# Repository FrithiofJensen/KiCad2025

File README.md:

# KiCad 2025 - Fra schematic til PCB til ESP-NOW RC System

Velkommen til materialerne for KiCad 2025 seminaret afholdt af Gert Lauritsen. Dette repository indeholder eksempler, projektfiler og Arduino-kode specifikt fokuseret på design af et printkort (PCB) til et fjernstyringssystem (RC) baseret på ESP-NOW protokollen.

Formålet med seminaret er at demonstrere designflowet i KiCad – fra skematisk diagram til færdigt PCB-layout – med et konkret projekt som eksempel: design af hardware til en ESP-NOW baseret sender eller modtager.

Vi vil se på, hvordan man designer et printkort, der integrerer en ESP32 microcontroller sammen med nødvendige komponenter som f.eks. input-enheder (joysticks, knapper) til en sender, eller output-drivere (servo-stik, motor-drivere) til en modtager. De medfølgende `.ino` filer implementerer selve ESP-NOW kommunikationen.

## Indhold

Repository'et indeholder (eller vil indeholde) følgende:

*   **KiCad Projektfiler:**
    *   Eksempler på skematiske diagrammer (`.kicad_sch`) for en RC-sender og/eller modtager.
    *   Eksempler på PCB layouts (`.kicad_pcb`) tilpasset ESP-moduler og RC-komponenter.
    *   Projektfil (`.kicad_pro`).
*   **Biblioteksfiler:**
    *   Specifikke symboler (`.kicad_sym`) og footprints (`.kicad_mod`) brugt i eksemplerne (hvis de ikke er standard i KiCad).
*   **ESP-NOW RC Arduino Sketches (`.ino`):**
    *   `RcRemote.ino`: Kode til ESP32 **senderen**. Læser typisk inputs (f.eks. fra potentiometre/joystick på det designede PCB) og sender data via ESP-NOW.
    *   `RCModtager.ino`: Kode til ESP32 **modtageren**. Modtager data via ESP-NOW og styrer outputs (f.eks. servoer eller motorer, potentielt via det designede PCB).
    *   Disse filer er beregnet til at blive kompileret og uploadet via Arduino IDE til separate ESP32 boards.
*   **Gerber/Produktionsfiler (Eksempel):**
    *   Eksempler på output-filer (`.gbr`, `.drl`) til PCB-produktion.

## Forudsætninger

For at få det fulde udbytte af seminaret og materialerne anbefales følgende software og hardware:

*   **Software:**
    *   **KiCad:**  Den seneste stabile version anbefales. Kan downloades gratis fra [https://www.kicad.org/](https://www.kicad.org/).
    *   **Arduino IDE:** Nødvendig for at arbejde med `.ino` filerne. Kan downloades gratis fra [https://www.arduino.cc/en/software](https://www.arduino.cc/en/software).
        *   **VIGTIGT:** Sørg for at have **ESP8266** og/eller **ESP32 board support** installeret i Arduino IDE via "Boards Manager". Se guides online, f.eks.:
            *   ESP32: [Howto install ESP32](https://randomnerdtutorials.com/installing-esp32-arduino-ide-2-0/)
        *   Tjek `.ino` filerne for eventuelle yderligere nødvendige Arduino libraries (ud over ESP-NOW, som er indbygget) og installer dem via "Library Manager".
*   **Hardware:**
    *   **Mindst to ESP32 boards** (f.eks. NodeMCU, ESP32 DevKitC) – ét til senderen og ét til modtageren for at kunne teste ESP-NOW kommunikationen.
    *   (Valgfrit) Komponenter til at bygge prototyper af sender/modtager (breadboard, ledninger, joysticks, potentiometre, servoer etc.).

## Brug af Materialerne

1.  **Klon eller Download:** Hent materialerne ned på din computer ved at klone repository'et (`git clone https://github.com/gert-lauritsen/KiCad2025.git`) eller downloade det som en ZIP-fil.
2.  **KiCad:** Åbn `.kicad_pro` filen i KiCad for at udforske skematik og PCB layout. Brug filerne som reference eller udgangspunkt for dit eget RC-hardware design.
3.  **Arduino / ESP-NOW:**
    *   Åbn `RcRemote.ino` i Arduino IDE.
    *   Åbn `RCModtager.ino` i et andet Arduino IDE vindue (eller efter hinanden).
    *   **Vigtigt:** ESP-NOW kræver, at enhederne kender hinandens MAC-adresser. Du skal typisk finde MAC-adressen på modtager-boardet og indsætte den i koden på sender-boardet (og/eller omvendt, afhængigt af koden). Find instruktioner til dette i kode-kommentarerne eller i ESP-NOW tutorials.
    *   Vælg det korrekte ESP32 board og port i "Tools" menuen for hvert board.
    *   Kompilér og upload sender-koden til det ene board.
    *   Kompilér og upload modtager-koden til det andet board.
    *   Test kommunikationen. Brug evt. Serial Monitor til debugging.

Vi håber, du får et lærerigt og udbytterigt seminar! Husk at installere KiCad, Arduino IDE og ESP board support *inden* seminaret starter for at få mest muligt ud af det.

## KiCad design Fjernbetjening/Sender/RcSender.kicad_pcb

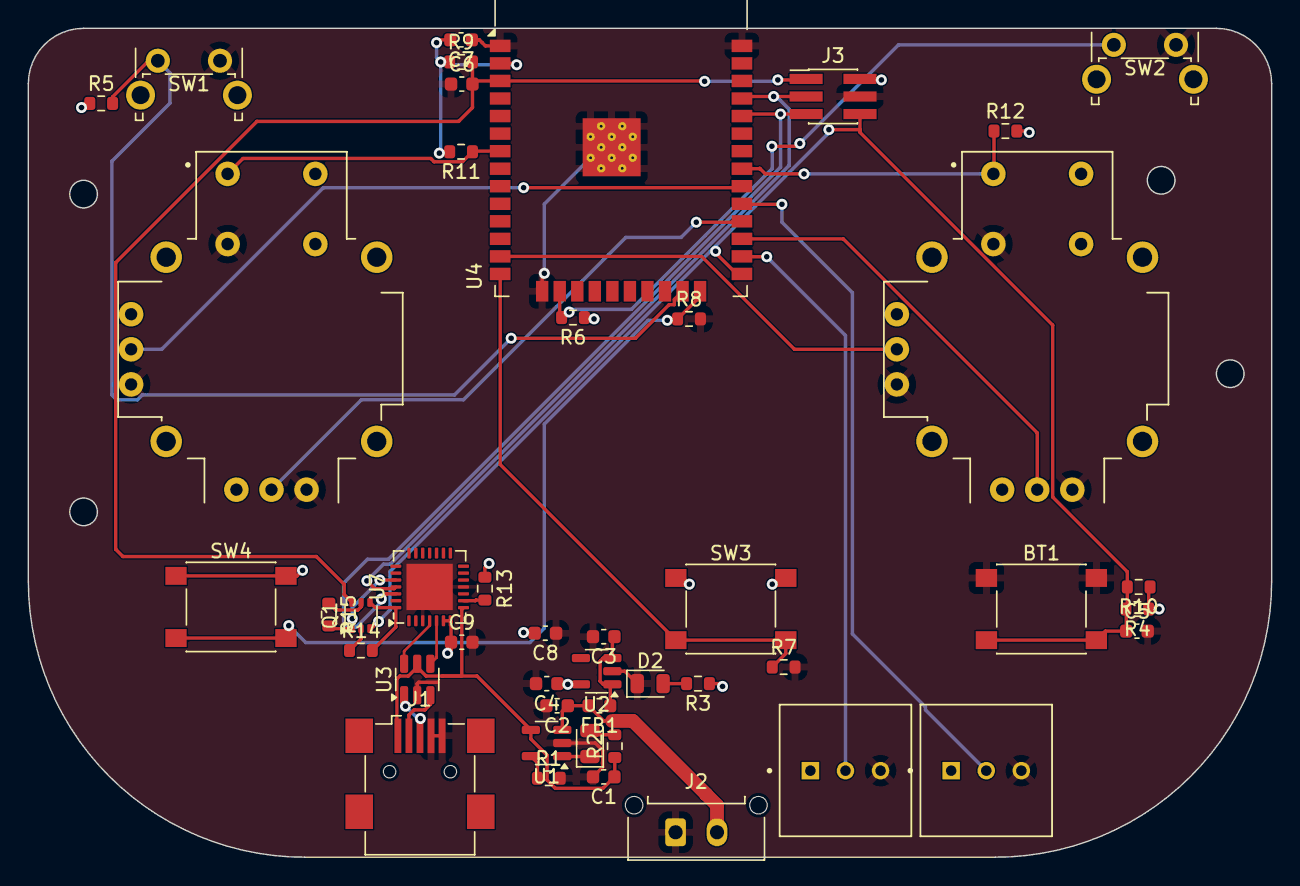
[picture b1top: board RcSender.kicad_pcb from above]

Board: 2 copper layers, 90.0 x 60.0 mm, 45 parts (0 on the bottom side), 34 nets.

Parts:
BT1: SW_Push; SW_SPST_PTS645
C1, C3, C4: 1uF; C_0603_1608Metric
C2: 10nF; C_0603_1608Metric
C5, C6, C7, C8: 0.1uf; C_0603_1608Metric
C9: 10u; C_0603_1608Metric
D1: Chrg; LED_0805_2012Metric
D2: PWR ON; LED_0805_2012Metric
FB1: Ferrite Bead; L_0603_1608Metric
J1: USB_A; USB_Mini-B_Wuerth_65100516121_Horizontal
J2: Bat; Molex_Micro-Fit_3.0_43650-0215_1x02_P3.00mm_Vertical
J3: Prog; PinHeader_2x03_P1.27mm_Vertical_SMD
POT1, POT2: COM-09806; POT-COM_09806
Q1: BC846BS; SOT-363_SC-70-6
R1: 2k; R_0603_1608Metric
R2, R3: 330; R_0603_1608Metric
R4, R5, R6, R7, R8, R11, R12: 4.7k; R_0603_1608Metric
R9, R10: 10K; R_0603_1608Metric
R13: 1k; R_0603_1608Metric
R14, R15: 10k; R_0603_1608Metric
SW1, SW2: SW_Push; SW_Tactile_SPST_Angled_PTS645Vx39-2LFS
SW3, SW4: SW_Push; SW_SPST_PTS645
U1: MCP73832-2-OT; SOT-23-5
U2: AP2112K-3.3; SOT-23-5
U3: USBLC6-2SC6; SOT-23-6
U4: ESP32-WROOM-32
U5, U6: COM-09032; POT-COM-09032
U7: CP2102N-Axx-xQFN28; QFN-28-1EP_5x5mm_P0.5mm_EP3.35x3.35mm

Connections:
+3.3V: C4.1, C7.2, C8.2, C9.1, J3.2, POT1.1, POT2.1, R3.1, R4.1, R5.1, R6.1, R9.1, R10.1, R11.2, R12.2, R13.1, SW3.1, SW4.1, U2.5 (VOUT), U4.2 (VDD), U5.H1 (H+), U5.V1 (V+), U6.H1 (H+), U6.V1 (V+), U7.6 (VDD), U7.7 (VREGIN)
+5V: C1.1, J1.1 (VBUS), R2.1, U1.4 (V_{DD}), U3.5 (VBUS), U7.8 (VBUS)
BT: BT1.2, C5.1, J3.6, Q1.3 (C2), R4.2, R10.2, U4.25 (IO0)
EN: C6.2, J3.1, Q1.6 (C1), R9.2, U4.3 (EN)
GND: BT1.1, C1.2, C2.2, C3.2, C4.2, C5.2, C6.1, C7.1, C8.1, C9.2, D2.1 (K), J1.4 (GND), J1.5 (Shield), J2.1, J3.4, POT1.3, POT2.3, R1.2, R7.2, R8.2, SW1.2, SW2.2, U1.2 (V_{SS}), U2.2 (GND), U3.2 (GND), U4.1 (GND), U4.15 (GND), U4.38 (GND), U4.39 (GND), U5.B2A (SEL-), U5.H3 (H-), U5.V3 (V-), U6.B2A (SEL-), U6.H3 (H-), U6.V3 (V-), U7.3 (GND), U7.11 (~SUSPEND), U7.29 (GND)
IO2: R8.1, SW4.2, U4.24 (IO2)
IO4: POT2.2, U4.26 (IO4)
IO5: POT1.2, U4.29 (IO5)
IO12: R7.1, SW3.2, U4.14 (IO12)
IO13: R6.2, SW2.1, U4.16 (IO13)
IO14: U4.13 (IO14), U6.V2 (V)
IO15: R5.2, SW1.1, U4.23 (IO15)
IO16: U4.27 (IO16), U6.H2 (H)
IO17: U4.28 (IO17), U5.H2 (H)
IO18: U4.30 (IO18), U5.V2 (V)
IO19: R12.1, U4.31 (IO19), U6.B1A (SEL+)
IO35: R11.1, U4.7 (IO35), U5.B1A (SEL+)
unnamed: D1.2 (A), R2.2
unnamed: D1.1 (K), U1.1 (STAT)
unnamed: D2.2 (A), R3.2
unnamed: J1.3 (D+), U3.1 (I/O1)
unnamed: J1.2 (D-), U3.3 (I/O2)
unnamed: Q1.2 (B1), R14.1
unnamed: Q1.1 (E1), R15.2, U7.24 (~RTS)
unnamed: Q1.5 (B2), R15.1
unnamed: Q1.4 (E2), R14.2, U7.28 (~DTR)
unnamed: R1.1, U1.5 (PROG)
unnamed: C3.1, FB1.1, U2.1 (VIN), U2.3 (EN)
unnamed: R13.2, U7.9 (~RST)
RX: J3.5, U4.34 (RXD0/IO3), U7.26 (TXD)
TX: J3.3, U4.35 (TXD0/IO1), U7.25 (RXD)
USBN: U3.4 (I/O2), U7.5 (D-)
USBP: U3.6 (I/O1), U7.4 (D+)
VIN: C2.1, FB1.2, J2.2, U1.3 (V_{BAT})

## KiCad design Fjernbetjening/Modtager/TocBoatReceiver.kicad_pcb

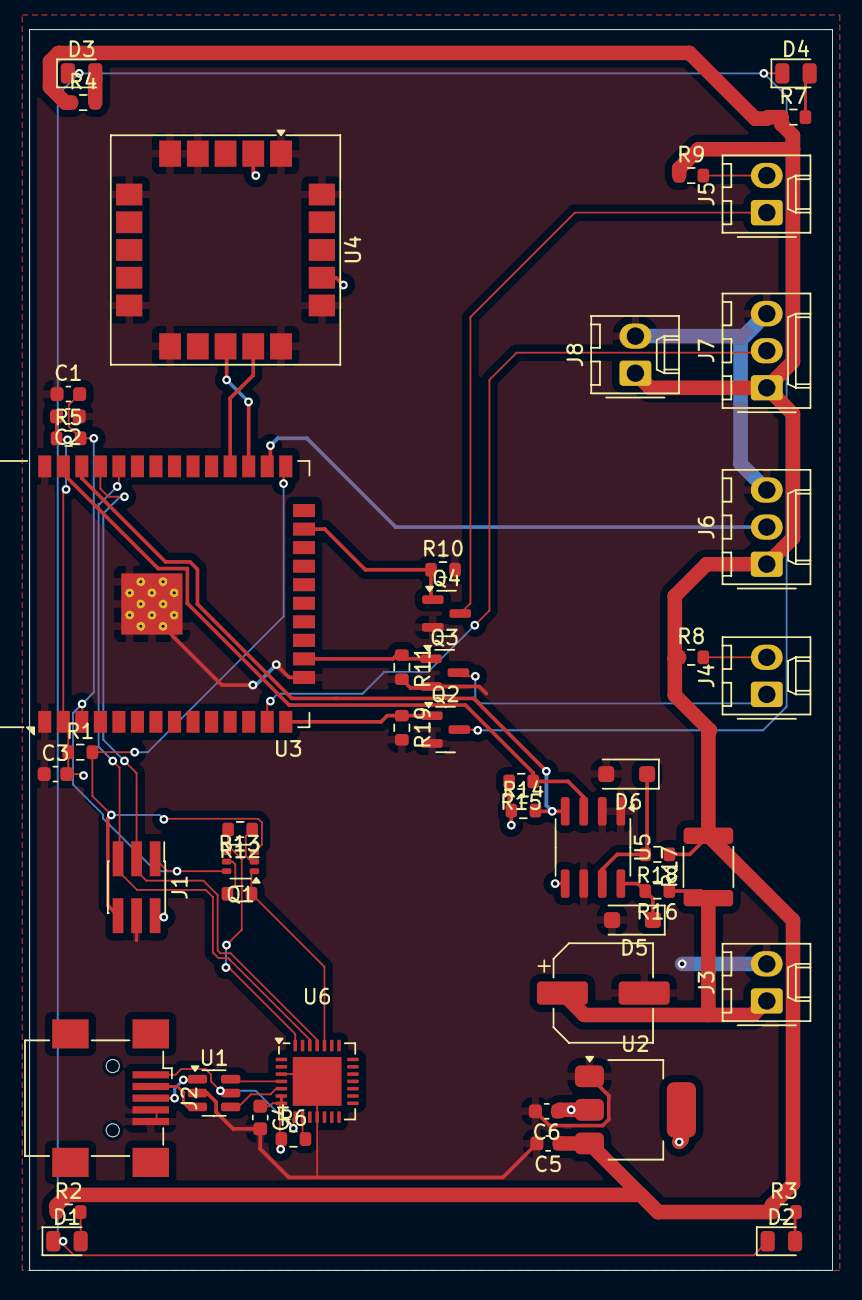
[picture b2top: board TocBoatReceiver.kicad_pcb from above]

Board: 2 copper layers, 55.0 x 85.0 mm, 50 parts (0 on the bottom side), 38 nets.

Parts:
C1, C2, C3: 0.1uf; C_0603_1608Metric
C4: 10u; C_0603_1608Metric
C5, C6: 1u; C_0603_1608Metric
C7: 100uF; CP_Elec_6.3x5.4
D1, D2, D3, D4: LED; LED_0805_2012Metric
D5, D6: BZT52B-C20; D_SOD-123F
J1: Prog; PinHeader_2x03_P1.27mm_Vertical_SMD
J2: USB_A; USB_Mini-B_Wuerth_65100516121_Horizontal
J3: Battery; Molex_KK-254_AE-6410-02A_1x02_P2.54mm_Vertical
J4, J5: Conn_01x02; Molex_KK-254_AE-6410-02A_1x02_P2.54mm_Vertical
J6: SpeedController; Molex_KK-254_AE-6410-03A_1x03_P2.54mm_Vertical
J7: Servo; Molex_KK-254_AE-6410-03A_1x03_P2.54mm_Vertical
J8: PowerESC; Molex_KK-254_AE-6410-02A_1x02_P2.54mm_Vertical
Q1: BC846BS; SOT-363_SC-70-6
Q2, Q3, Q4: AO3400A; SOT-23
R1, R5, R10, R11, R14, R15, R19: 10K; R_0603_1608Metric
R2, R3, R4, R6, R7, R8, R9: 1k; R_0603_1608Metric
R12, R13: 10k; R_0603_1608Metric
R16, R18: 100; R_0603_1608Metric
R17: 0.01R; R_1812_4532Metric
U1: USBLC6-2SC6; SOT-23-6
U2: AP1117-33; SOT-223-3_TabPin2
U3: ESP32-WROOM-32
U4: SAM-M8Q; ublox_SAM-M8Q
U5: INA219BxD; SOIC-8_3.9x4.9mm_P1.27mm
U6: CP2102N-Axx-xQFN28; QFN-28-1EP_5x5mm_P0.5mm_EP3.35x3.35mm

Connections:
+3.3V: C2.2, C3.2, C4.1, C6.1, J1.2, R1.1, R5.1, R6.1, R14.1, R15.2, U2.2 (VO), U3.2 (VDD), U4.2 (VCC_IO), U4.17 (VCC), U5.5 (VS), U6.6 (VDD), U6.7 (VREGIN)
+5V: J2.1 (VBUS), U1.5 (VBUS), U6.8 (VBUS)
+BATT: C5.1, J6.1, J7.1, J8.1, R2.1, R3.1, R4.1, R7.1, R8.1, R9.1, R17.2, R18.1, U2.3 (VI)
/ESP32/GPIO4: J6.2, U3.26 (IO4)
/ESP32/GPIO12: Q2.1 (G), R19.1, U3.14 (IO12)
/ESP32/GPIO13: Q3.1 (G), R11.1, U3.16 (IO13)
/ESP32/GPIO14: J7.2, U3.13 (IO14)
/ESP32/GPIO15: Q4.1 (G), R10.1, U3.23 (IO15)
/ESP32/GPIO16: U3.27 (IO16), U4.13 (TXD)
/ESP32/GPIO17: U3.28 (IO17), U4.14 (RXD)
/ESP32/SCL: R14.2, U3.36 (IO22), U5.4 (SCL)
/ESP32/SDA: R15.1, U3.37 (IO23), U5.3 (SDA)
/USB Serial/USB_N: U1.4 (I/O2), U6.5 (D-)
/USB Serial/USB_P: U1.6 (I/O1), U6.4 (D+)
D0: J1.6, Q1.3 (C2), R1.2, U3.25 (IO0)
EN: C1.2, J1.1, Q1.6 (C1), R5.2, U3.3 (EN)
GND: C1.1, C2.1, C3.1, C4.2, C5.2, C6.2, C7.2, D5.2 (A), D6.2 (A), J1.4, J2.4 (GND), J2.5 (Shield), J3.2, J6.3, J7.3, J8.2, Q2.2 (S), Q3.2 (S), Q4.2 (S), R10.2, R11.2, R19.2, U1.2 (GND), U2.1 (GND), U3.1 (GND), U3.15 (GND), U3.38 (GND), U3.39 (GND), U4.1 (GND), U4.4 (GND), U4.5 (GND), U4.6 (GND), U4.10 (GND), U4.11 (GND), U4.15 (GND), U4.16 (GND), U4.20 (GND), U5.1 (A1), U5.2 (A0), U5.6 (GND), U6.3 (GND), U6.11 (~SUSPEND), U6.29 (GND)
unnamed: D1.2 (A), R2.2
unnamed: D1.1 (K), D2.1 (K), D3.1 (K), D4.1 (K), Q2.3 (D)
unnamed: D2.2 (A), R3.2
unnamed: D3.2 (A), R4.2
unnamed: D4.2 (A), R7.2
unnamed: D5.1 (K), R16.2, U5.8 (IN+)
unnamed: D6.1 (K), R18.2, U5.7 (IN-)
unnamed: J2.3 (D+), U1.1 (I/O1)
unnamed: J2.2 (D-), U1.3 (I/O2)
unnamed: C7.1, J3.1, R16.1, R17.1
unnamed: J4.1, Q3.3 (D)
unnamed: J4.2, R8.2
unnamed: J5.1, Q4.3 (D)
unnamed: J5.2, R9.2
unnamed: Q1.2 (B1), R12.1
unnamed: Q1.1 (E1), R13.2, U6.24 (~RTS)
unnamed: Q1.5 (B2), R13.1
unnamed: Q1.4 (E2), R12.2, U6.28 (~DTR)
unnamed: R6.2, U6.9 (~RST)
RX: J1.5, U3.34 (RXD0/IO3), U6.26 (TXD)
TX: J1.3, U3.35 (TXD0/IO1), U6.25 (RXD)

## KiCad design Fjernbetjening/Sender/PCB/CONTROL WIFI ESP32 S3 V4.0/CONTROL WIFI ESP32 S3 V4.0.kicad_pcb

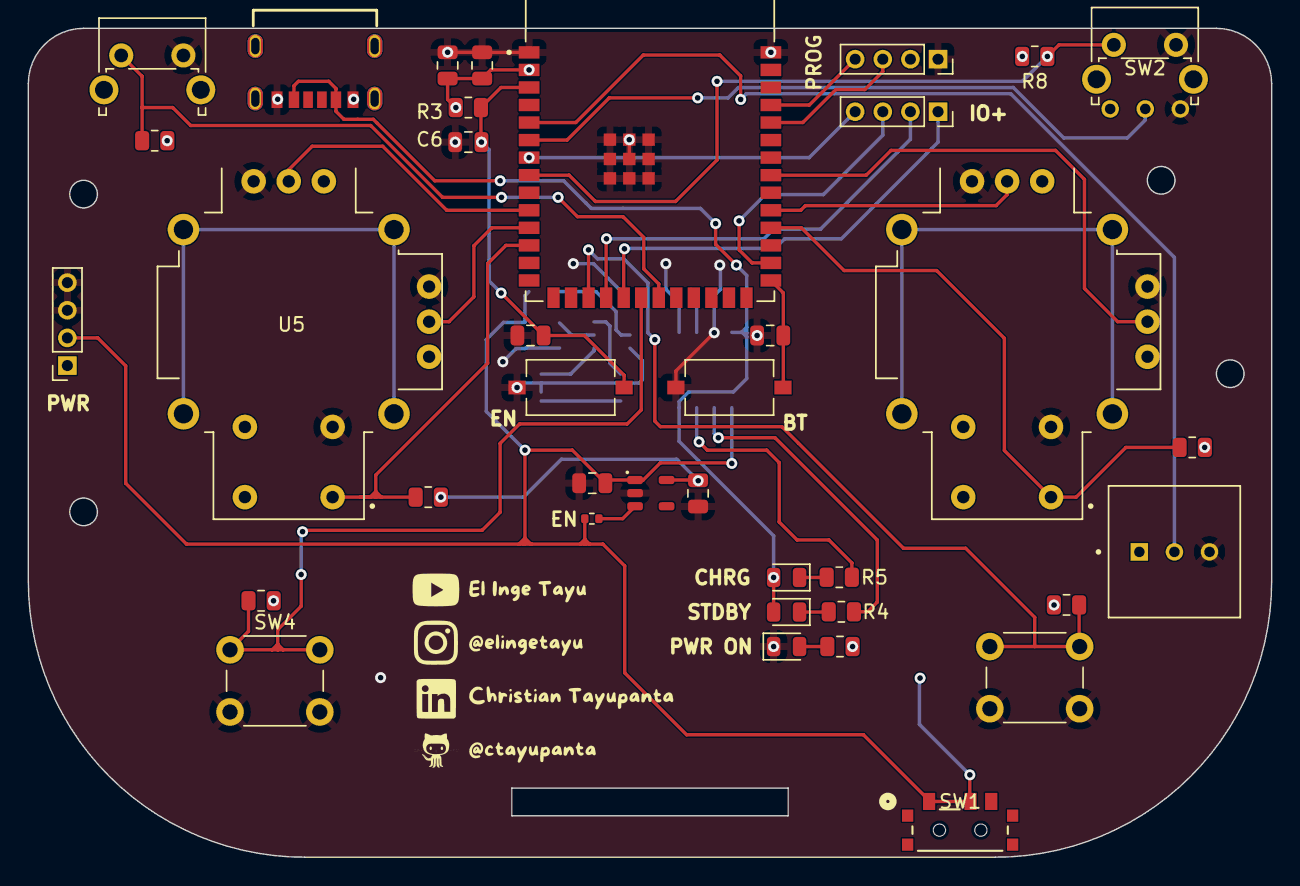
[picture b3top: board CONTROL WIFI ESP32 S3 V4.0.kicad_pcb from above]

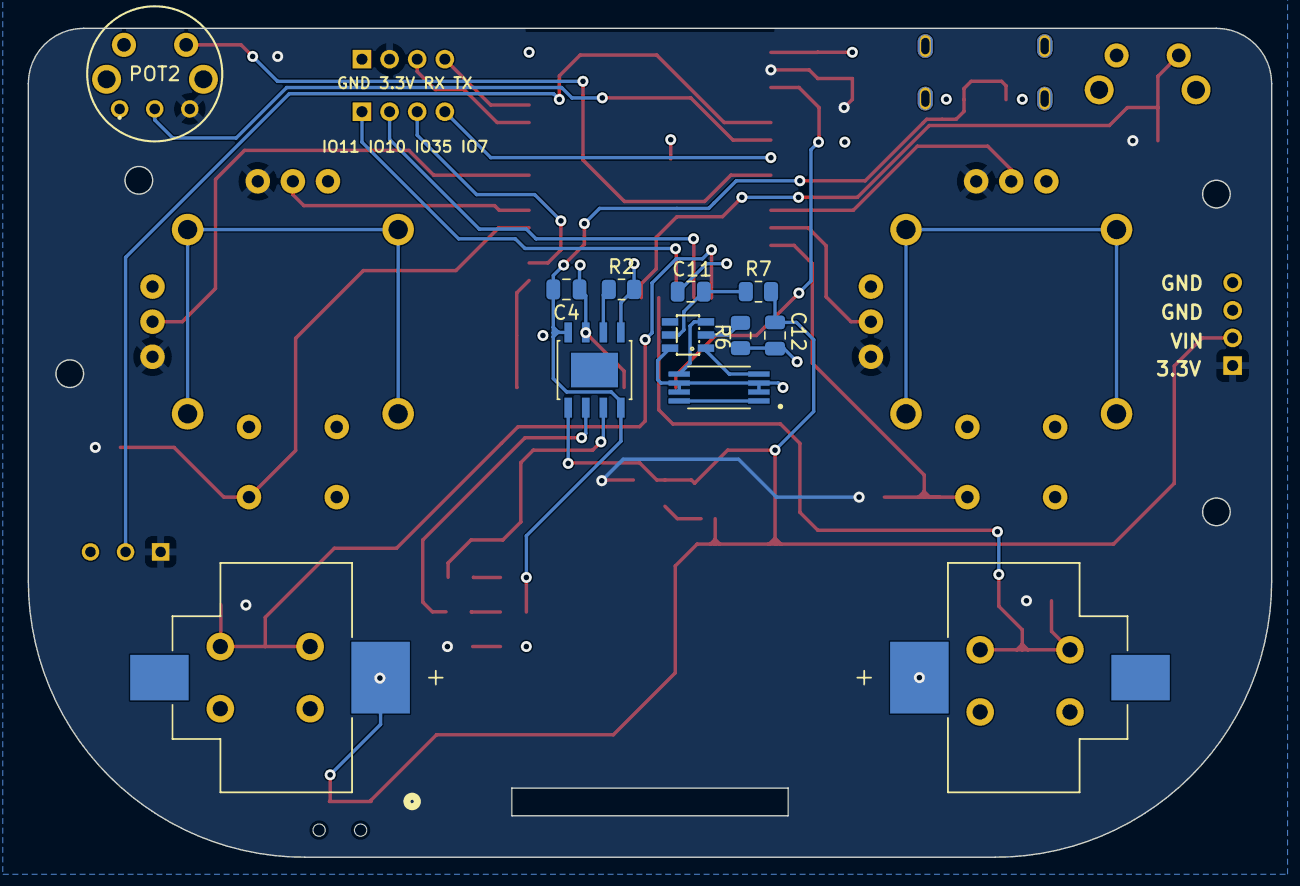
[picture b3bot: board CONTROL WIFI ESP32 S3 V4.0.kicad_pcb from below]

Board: 2 copper layers, 90.0 x 60.0 mm, 49 parts (12 on the bottom side), 36 nets.

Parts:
BT1, BT2: 254TR; BAT_254TR
BT3: SW_Push; SW_Tactile_SPST_NO_Straight_CK_PTS636Sx25SMTRLFS
C1, C2: 1uF; C_0805_2012Metric
C4, C12: 10uF; C_0805_2012Metric
C6, C7, C8, C9, C10: 0.1uf; C_0805_2012Metric
C11: 0.1uF; C_0805_2012Metric
CHRG1: R 1K; LED_0805_2012Metric
D1: PWR ON; LED_0805_2012Metric
EN1: SW_Push; SW_Tactile_SPST_NO_Straight_CK_PTS636Sx25SMTRLFS
IC1: DW01A; DW01A SOT23-6
J1: PW; PinSocket_1x04_P2.00mm_Vertical
J3: IO+; PinSocket_1x04_P2.00mm_Vertical
J4: PROG; PinSocket_1x04_P2.00mm_Vertical
J5: USB4125-GF-A_REVA2; GCT_USB4125-GF-A_REVA2
POT1: COM-09806; POT-COM_09806
POT2: 91AR1KLF; THUMBWHEEL POT 1K
Q1: FS8205A; SOP65P640X120-8N
R1: 330; R_0805_2012Metric
R2: 1,2K; R_0805_2012Metric
R3: 10K; R_0805_2012Metric
R4, R5: 1k; R_0805_2012Metric
R6: 1K; R_0805_2012Metric
R7: 100; R_0805_2012Metric
R8, R9, R10, R11, R12, R13: 4.7k; R_0805_2012Metric
R14: R; R_0402_1005Metric
STDBY1: G 1K; LED_0805_2012Metric
SW1: SLW-66527511-SMT-TR; SLW-66527511-SMT-TR_CUD
SW2, SW3: SW_Push; SW_Tactile_SPST_Angled_PTS645Vx83-2LFS
SW4, SW5: SW_Push; SW_PUSH_6mm_H4.3mm
U1: MIC5504-1.8YM5-TR; SOT23-5P95_280X145XL45X37N
U2: TP4056
U3: ESP32-S3-WROOM-1-N8R8
U4, U5: COM-09032; POT-COM-09032

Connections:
+3.3V: C1.1, C7.2, C8.2, J1.1, J4.2, POT1.1, POT2.3, R1.1, R3.1, R8.1, R9.1, R10.1, R11.1, R12.1, R13.1, U1.5 (VOUT), U3.2 (3V3), U4.H1 (H+), U4.V1 (V+), U5.H1 (H+), U5.V1 (V+)
BT: BT3.2, C10.1, U3.27 (IO0)
EN: C6.2, C9.1, EN1.2, R3.2, U3.3 (EN)
GND: BT1.P1, BT3.1, C1.2, C2.2, C4.1, C6.1, C7.1, C8.1, C9.2, C10.2, C11.2, C12.2, D1.1 (K), EN1.1, IC1.6 (GND), J1.3, J1.4, J4.1, J5.A12 (GND), J5.B12 (GND__1), POT1.3, POT2.1, Q1.2, Q1.3, Q1.6, Q1.7, R2.2, R6.2, SW2.2, SW3.2, SW4.2, SW5.2, U1.2 (GND), U2.1 (TEMP), U2.3 (GND), U3.1 (GND), U3.40 (GND), U3.41_1 (GND), U3.41_2 (GND), U3.41_3 (GND), U3.41_4 (GND), U3.41_5 (GND), U3.41_6 (GND), U3.41_7 (GND), U3.41_8 (GND), U3.41_9 (GND), U4.B2A (SEL-), U4.H3 (H-), U4.V3 (V-), U5.B2A (SEL-), U5.H3 (H-), U5.V3 (V-)
IO5: POT1.2, U3.5 (IO5)
IO6: POT2.2, U3.6 (IO6)
IO7: J3.4, U3.7 (IO7)
IO8: R13.2, U3.12 (IO8), U5.B1A (SEL+)
IO9: R11.2, SW5.1, U3.17 (IO9)
IO10: J3.2, U3.18 (IO10)
IO11: J3.1, U3.19 (IO11)
IO12: R10.2, SW4.1, U3.20 (IO12)
IO13: R9.2, SW3.1, U3.21 (IO13)
IO15: R8.2, SW2.1, U3.8 (IO15)
IO17: U3.10 (IO17), U5.H2 (H)
IO18: U3.11 (IO18), U5.V2 (V)
IO35: J3.3, U3.28 (IO35)
IO37: R12.2, U3.30 (IO37), U4.B1A (SEL+)
IO38: U3.31 (IO38), U4.H2 (H)
IO40: U3.33 (IO40), U4.V2 (V)
unnamed: C4.2, CHRG1.2 (A), J5.A9 (VBUS), J5.B9 (VBUS__1), STDBY1.2 (A), U2.4 (VCC), U2.8 (CE)
unnamed: CHRG1.1 (K), R5.2
unnamed: D1.2 (A), R1.2
unnamed: IC1.2 (CS), R6.1
unnamed: IC1.3 (OC), Q1.5
unnamed: IC1.1 (OD), Q1.4
unnamed: C11.1, IC1.5 (VCC), R7.1
unnamed: Q1.1, Q1.8
unnamed: R4.2, STDBY1.1 (K)
unnamed: R14.2, U1.3 (EN)
unnamed: R5.1, U2.7 (*CHRG)
unnamed: R4.1, U2.6 (*STDBY)
unnamed: R2.1, U2.2 (PROG)
RX: J4.3, U3.36 (RXD0)
TX: J4.4, U3.37 (TXD0)
VIN: BT2.P1, C2.1, C12.1, J1.2, R7.2, R14.1, SW1.1, SW1.2, U1.1 (VIN), U2.5 (BAT)

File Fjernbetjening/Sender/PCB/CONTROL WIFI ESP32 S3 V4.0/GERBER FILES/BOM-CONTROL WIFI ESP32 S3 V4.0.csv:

"Reference","Value","Footprint","LINK","Qty"
"BT1, BT2","254TR","BAT_254TR:BAT_254TR","https://www.digikey.com/en/products/detail/keystone-electron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","2"
"BT3","SW_Push","Button_Switch_SMD:SW_Tactile_SPST_NO_Straight_CK_PTS636Sx25SMTRLFS","https://www.digikey.com/en/products/detail/c-k/PTS636-SK25-S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","1"
"C1, C2","1uF","Capacitor_SMD:C_0805_2012Metric","","2"
"C4, C12","10uF","Capacitor_SMD:C_0805_2012Metric","https://www.digikey.com/en/products/detail/samsung-electro-m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","2"
"C6-C10","0.1uf","Capacitor_SMD:C_0805_2012Metric","https://www.digikey.com/en/products/detail/samsung-electro-m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","5"
"C11","0.1uF","Capacitor_SMD:C_0805_2012Metric","https://www.digikey.com/en/products/detail/samsung-electro-m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","1"
"CHRG1","R 1K","LED_SMD:LED_0805_2012Metric","https://www.digikey.com/en/products/detail/w%C3%BCrth-elektr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","1"
"D1","PWR ON","LED_SMD:LED_0805_2012Metric","https://www.digikey.com/en/products/detail/w%C3%BCrth-elektr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","1"
"EN1","SW_Push","Button_Switch_SMD:SW_Tactile_SPST_NO_Straight_CK_PTS636Sx25SMTRLFS","https://www.digikey.com/en/products/detail/c-k/PTS636-SK25-S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","1"
"IC1","DW01A","DW01A:DW01A SOT23-6","","1"
"J1","PW","Connector_PinSocket_2.00mm:PinSocket_1x04_P2.00mm_Vertical","","1"
"J3","IO+","Connector_PinSocket_2.00mm:PinSocket_1x04_P2.00mm_Vertical","","1"
"J4","PROG","Connector_PinSocket_2.00mm:PinSocket_1x04_P2.00mm_Vertical","","1"
"J5","USB4125-GF-A_REVA2","USB-C-GCT_USB4125-GF-A:GCT_USB4125-GF-A_REVA2","https://www.digikey.com/en/products/detail/gct/USB4125-GF-A/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","1"
"POT1","COM-09806","POT-COM_09806:POT-COM_09806","https://www.digikey.com/en/products/detail/sparkfun-electron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","1"
"POT2","91AR1KLF","THUMBWHEELPOT1K:THUMBWHEEL POT 1K","https://www.digikey.com/en/products/detail/tt-electronics-bi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","1"
"Q1","FS8205A","FS8205A:SOP65P640X120-8N","","1"
"R1","330","Resistor_SMD:R_0805_2012Metric","https://www.digikey.com/en/products/detail/yageo/RC0805FR-07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","1"
"R2","1,2K","Resistor_SMD:R_0805_2012Metric","https://www.digikey.com/en/products/detail/te-connectivity-p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","1"
"R3","10K","Resistor_SMD:R_0805_2012Metric","https://www.digikey.com/en/products/detail/stackpole-electro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","1"
"R4, R5","1k","Resistor_SMD:R_0805_2012Metric","https://www.digikey.com/en/products/detail/yageo/RC0805FR-07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","2"
"R6","1K","Resistor_SMD:R_0805_2012Metric","https://www.digikey.com/en/products/detail/yageo/RC0805FR-07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","1"
"R7","100","Resistor_SMD:R_0805_2012Metric","https://www.digikey.com/en/products/detail/yageo/RC0805FR-07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","1"
"R8-R13","4.7k","Resistor_SMD:R_0805_2012Metric","https://www.digikey.com/en/products/detail/vishay-dale/CRCW0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","6"
"R14","R","Resistor_SMD:R_0402_1005Metric","DNP","1"
"STDBY1","G 1K","LED_SMD:LED_0805_2012Metric","https://www.digikey.com/en/products/detail/w%C3%BCrth-elektr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","1"
"SW1","SLW-66527511-SMT-TR","SW-SLIDE:SLW-66527511-SMT-TR_CUD","https://www.digikey.com/en/products/detail/cui-devices/SLW-6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","1"
"SW2, SW3","SW_Push","Button_Switch_THT:SW_Tactile_SPST_Angled_PTS645Vx83-2LFS","https://www.digikey.com/en/products/detail/c-k/PTS645VH83-2-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","2"
"SW4, SW5","SW_Push","Button_Switch_THT:SW_PUSH_6mm_H4.3mm","","2"
"U1","MIC5504-1.8YM5-TR","MIC5504-1.8YM5-TR:SOT23-5P95_280X145XL45X37N","https://www.digikey.com/en/products/detail/microchip-technol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","1"
"U2","TP4056","TP4056:TP4056","","1"
"U3","ESP32-S3-WROOM-1-N8R8","ESP32-S3:ESP32-S3-WROOM-1-N8R8","https://www.digikey.com/en/products/detail/espressif-systems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","1"
"U4, U5","COM-09032","POT-COM-09032:POT-COM-09032","https://www.digikey.com/en/products/detail/sparkfun-electron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","2"

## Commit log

2025-03-23 init
2025-03-25 mods on PCB done
2025-03-27 firmware oplæg added
2025-03-27 powerpoint update
2025-03-28 S2 version sender data og modtages på devboard
2025-03-29 S2 version
2025-03-29 Opgaver tilføjet
2025-03-30 Oprydning
2025-03-30 Servo and ESC working
2025-04-06 forberedelse for drone

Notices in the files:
parts and their libraries:
Copyright 2021 Accelerated Designs. All rights reserved.
